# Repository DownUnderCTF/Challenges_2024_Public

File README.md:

<div align="center">

![banner][banner]

Files + Solutions for DownUnderCTF 2024 Challenges

[Website][website] | [CTFTime][ctftime] | [Discord][discord] | [Twitter][twitter]

[banner]: https://files.catbox.moe/vlniki.png
[website]: https://downunderctf.com
[ctftime]: https://ctftime.org/event/2284
[discord]: https://duc.tf/discord
[twitter]: https://twitter.com/downunderctf

</div>

---

# beginner
|                             Challenge                              |   Author   | Category | Solves |
| ------------------------------------------------------------------ | ---------- | -------- | -----: |
| [tldr please summarise](./beginner/tldr-please-summarise)          | Nosurf     | misc     |   1081 |
| [parrot the emu](./beginner/parrot-the-emu)                        | richighimi | web      |    993 |
| [Sun Zi's Perfect Math Class](./beginner/sunzi-perfect-math-class) | wednesday  | crypto   |    801 |
| [zoo feedback form](./beginner/zoo-feedback-form)                  | richighimi | web      |    693 |
| [shufflebox](./beginner/shufflebox)                                | hashkitten | crypto   |    582 |
| [number mashing](./beginner/number-mashing)                        | joseph     | rev      |    299 |
| [Intercepted Transmissions](./beginner/intercepted-transmissions)  | Pix        | misc     |    275 |
| [vector overflow](./beginner/vector-overflow)                      | joseph     | pwn      |    239 |
| [yawa](./beginner/yawa)                                            | joseph     | pwn      |    184 |
| [sssshhhh](./beginner/sssshhhh)                                    | Pix        | rev      |     81 |

# crypto
|                          Challenge                          |   Author   | Difficulty | Solves |
| ----------------------------------------------------------- | ---------- | ---------- | -----: |
| [decrypt then eval](./crypto/decrypt-then-eval)             | joseph     | easy       |    197 |
| [my array generator](./crypto/my-array-generator)           | wednesday  | easy       |     60 |
| [V for Vieta](./crypto/v-for-vieta)                         | wednesday  | easy       |     55 |
| [three line crypto](./crypto/three-line-crypto)             | hashkitten | medium     |     44 |
| [super party computation](./crypto/super-party-computation) | wednesday  | medium     |     13 |
| [Poly1305 OTM](./crypto/poly1305-otm)                       | joseph     | medium     |      6 |
| [AES](./crypto/aes)                                         | wednesday  | hard       |      2 |
| [kyber decryption oracle](./crypto/kyber-decryption-oracle) | joseph     | hard       |      1 |

# pwn
|                       Challenge                        |     Author      | Difficulty | Solves |
| ------------------------------------------------------ | --------------- | ---------- | -----: |
| [sign in](./pwn/sign-in)                               | joseph          | easy       |     95 |
| [pac shell](./pwn/pac-shell)                           | joseph          | easy       |     55 |
| [sheep farm simulator](./pwn/sheep-farm-simulator)     | joseph          | medium     |     21 |
| [Faulty Kernel](./pwn/faulty-kernel)                   | toasterpwn      | hard       |     15 |
| [ESPecially secure boot](./pwn/especially-secure-boot) | joseph, HexF    | medium     |      3 |
| [mirage](./pwn/mirage)                                 | grub and anvbis | hard       |      1 |

# rev
|                            Challenge                             |        Author         | Difficulty | Solves |
| ---------------------------------------------------------------- | --------------------- | ---------- | -----: |
| [rusty vault](./rev/rusty-vault)                                 | 1nval1d (Cybears)     | easy       |     81 |
| [jmp flag](./rev/jmp-flag)                                       | joseph                | easy       |     71 |
| [pressing buttons](./rev/pressing-buttons)                       | joseph                | medium     |     34 |
| [dungeon](./rev/dungeon)                                         | joseph                | medium     |     22 |
| [Ternary Brained](./rev/ternary-brained)                         | @jscarsbrook and @pix | medium     |     15 |
| [average assembly assignment](./rev/average-assembly-assignment) | joseph                | medium     |     13 |
| [adorable encrypted animal](./rev/adorable-encrypted-animal)     | joseph                | hard       |      3 |

# web
|                   Challenge                    |    Author    | Difficulty | Solves |
| ---------------------------------------------- | ------------ | ---------- | -----: |
| [co2](./web/co2)                               | n00b.master. | easy       |    289 |
| [hah got em](./web/hah-got-em)                 | ghostccamm   | easy       |    173 |
| [i am confusion](./web/i-am-confusion)         | richighimi   | medium     |    113 |
| [co2v2](./web/co2v2)                           | n00b.master. | medium     |     59 |
| [sniffy](./web/sniffy)                         | hashkitten   | easy       |     58 |
| [waifu](./web/waifu)                           | ghostccamm   | medium     |     20 |
| [Prisoner Processor](./web/prisoner-processor) | ghostccamm   | hard       |     17 |

# hardware
|                 Challenge                 |   Author    | Difficulty | Solves |
| ----------------------------------------- | ----------- | ---------- | -----: |
| [Sounds Nice](./hardware/sounds-nice)     | HexF        | easy       |    125 |
| [I See](./hardware/i-see)                 | HexF        | easy       |     61 |
| [The Door](./hardware/the-door)           | HexF        | medium     |     15 |
| [Crash Landing](./hardware/crash-landing) | HexF        | medium     |     12 |
| [sirkit](./hardware/sirkit)               | HexF        | hard       |      4 |
| [Birdloader](./hardware/birdloader)       | HexF, Jamie | medium     |      2 |
| [DUCTF](./hardware/ductf)                 | HexF        | hard       |      0 |

# forensics
|                          Challenge                          |       Author       | Difficulty | Solves |
| ----------------------------------------------------------- | ------------------ | ---------- | -----: |
| [Baby's First Forensics](./forensics/babys-first-forensics) | Pix                | beginner   |    920 |
| [SAM I AM](./forensics/samiam)                              | TurboPenguin       | beginner   |    545 |
| [Bad Policies](./forensics/badpolicies)                     | TurboPenguin       | beginner   |    386 |
| [Macro Magic](./forensics/macromagic)                       | TurboPenguin & Pix | easy       |    146 |
| [emuc2](./forensics/emuc2)                                  | BootlegSorcery@    | easy       |    117 |
| [Lost in Memory](./forensics/lostinmemory)                  | TurboPenguin       | medium     |     42 |

# osint
|                       Challenge                        |   Author   | Difficulty | Solves |
| ------------------------------------------------------ | ---------- | ---------- | -----: |
| [offtheramp](./osint/offtheramp)                       | Anon       | beginner   |    851 |
| [cityviews](./osint/cityviews)                         | Anon       | easy       |    631 |
| [Bridget Lives](./osint/bridget-lives)                 | a_metre    | easy       |    505 |
| [back to the jungle](./osint/back-to-the-jungle)       | ghostccamm | easy       |    460 |
| [They're Making Decoys](./osint/they-re-making-decoys) | Nosurf     | medium     |    190 |
| [marketing](./osint/marketing)                         | ghostccamm | beginner   |    187 |

# misc
|                       Challenge                       |        Author         | Difficulty | Solves |
| ----------------------------------------------------- | --------------------- | ---------- | -----: |
| [discord](./misc/discord)                             | DUCTF                 | beginner   |    855 |
| [survey](./misc/survey)                               | DUCTF                 | beginner   |    446 |
| [Wacky Recipe](./misc/wackyrecipe)                    | TurboPenguin & joseph | easy       |    152 |
| [DNAdecay](./misc/dnadecay)                           | BootlegSorcery@       | easy       |    148 |
| [WebSocket VPN](./misc/wsvpn)                         | jscarsbrook           | medium     |     23 |
| [the other minimal php](./misc/the-other-minimal-php) | hashkitten            | medium     |     22 |
| [mkductfiso](./misc/mkductfiso)                       | Pix && joseph         | medium     |     19 |
| [pkijs<](./misc/pkijs-lt)                             | joseph                | medium     |      7 |
| [pkijs=](./misc/pkijs-eq)                             | joseph                | medium     |      1 |

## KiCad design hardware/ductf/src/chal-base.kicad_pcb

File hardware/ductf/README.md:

# DUCTF

This challenge involves an attack on the DESFire protocol, when the random nonce generated by the reader is known.
The random nonce in this case is generated using the hardware randomness of the RP2040.
In the RP2040, if the CPU clock is a harmonic of the internal ring oscillator, the random number generator is entirely predictable (yielding either all 1s or all 0s).

We can then use the reader as an encryption primitive through its use of CBC encryption to forge a DESFire session key with the reader.
We can thus communicate with the reader, which will write the flag to our card.

**Category**: Hardware / Crypto

**Difficulty**: Hard

**Author**: HexF

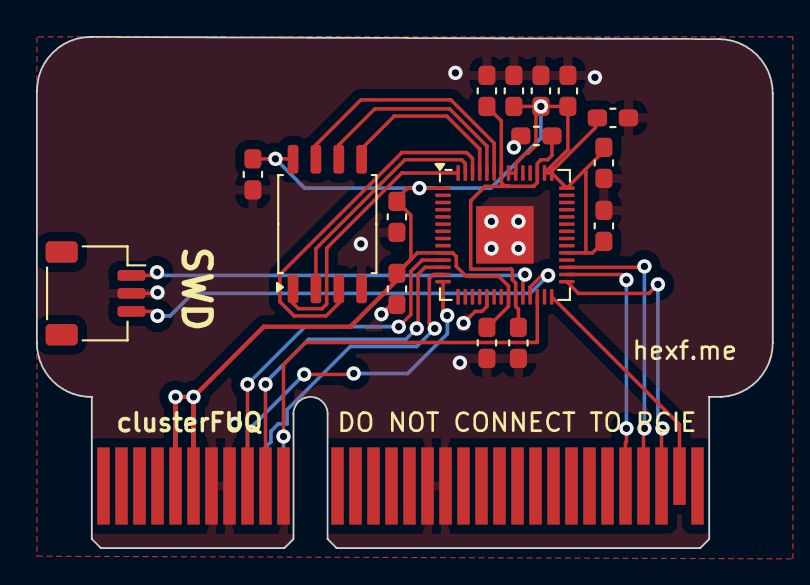
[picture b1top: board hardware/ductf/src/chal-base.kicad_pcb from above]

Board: 2 copper layers, 40.9 x 28.4 mm, 17 parts (0 on the bottom side), 20 nets.

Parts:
C101, C103, C104, C105, C106, C107, C108, C109, C110, C111, C112: 100nF; C_0603_1608Metric_Pad1.08x0.95mm_HandSolder
C102, C113: 1uF; C_0603_1608Metric_Pad1.08x0.95mm_HandSolder
J1: clusterFUQ_Connector; BUS_PCIexpress_x4
J101: Conn_01x03_Pin; JST_SH_SM03B-SRSS-TB_1x03-1MP_P1.00mm_Horizontal
U101: RP2040; QFN-56-1EP_7x7mm_P0.4mm_EP3.2x3.2mm
U102: W25Q16JVSS; SOIC-8_5.23x5.23mm_P1.27mm

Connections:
+3V3: C101.1, C102.1, C103.1, C104.1, C105.1, C106.1, C107.1, C108.1, C109.1, C110.1, J1.A5 (+3V3), J1.A6 (+3V3), J1.B5 (+3V3), J1.B6 (+3V3), U101.1 (IOVDD), U101.10 (IOVDD), U101.22 (IOVDD), U101.33 (IOVDD), U101.42 (IOVDD), U101.43 (ADC_AVDD), U101.44 (VREG_IN), U101.48 (USB_VDD), U101.49 (IOVDD), U102.8 (VCC)
/CH_CS: J1.B10 (CS), U101.12 (GPIO9)
/CH_MISO: J1.A9 (MISO), U101.14 (GPIO11)
/CH_MOSI: J1.B9 (MOSI), U101.11 (GPIO8)
/CH_SCK: J1.A10 (SCK), U101.13 (GPIO10)
/MISO: J1.B29 (IO19), U101.31 (GPIO20)
/MOSI: J1.B28 (IO20), U101.30 (GPIO19)
/QSPI.CK: U101.52 (QSPI_SCLK), U102.6 (CLK)
/QSPI.D0: U101.53 (QSPI_SD0), U102.5 (DI(IO0))
/QSPI.D1: U101.55 (QSPI_SD1), U102.2 (DO(IO1))
/QSPI.D2: U101.54 (QSPI_SD2), U102.3 (~WP(IO2))
/QSPI.D3: U101.51 (QSPI_SD3), U102.7 (~RESET(IO3))
/QSPI.SS: U101.56 (QSPI_SS), U102.1 (~CS)
/RC522_CS: J1.B31 (IO17), U101.28 (GPIO17)
/SCK: J1.B30 (IO18), U101.29 (GPIO18)
/~RESET: J1.A11 (~RESET), U101.26 (RUN)
GND: C101.2, C102.2, C103.2, C104.2, C105.2, C106.2, C107.2, C108.2, C109.2, C110.2, C111.1, C112.1, C113.1, J1.A7 (GND), J1.A8 (GND), J1.B7 (GND), J1.B8 (GND), J1.B11 (GND), J1.B17 (GND), J1.B18 (GND), J101.2, U101.19 (TESTEN), U101.57 (GND), U102.4 (GND)
unnamed: J101.1, U101.24 (SWCLK)
unnamed: J101.3, U101.25 (SWD)
unnamed: C111.2, C112.2, C113.2, U101.23 (DVDD), U101.45 (VREG_VOUT), U101.50 (DVDD)

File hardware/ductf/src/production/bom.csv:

Designator,Footprint,Quantity,Value,LCSC Part #
"C101, C103, C104, C105, C106, C107, C108, C109, C110, C111, C112",0603,11,100nF,C14663
"C102, C113",0603,2,1uF,C15849
J101,JST_SH_SM03B-SRSS-TB_1x03-1MP_P1.00mm_Horizontal,1,Conn_01x03_Pin,C160403
U101,QFN-56-1EP_7x7mm_P0.4mm_EP3.2x3.2mm,1,RP2040,
U102,SOIC-8_5.23x5.23mm_P1.27mm,1,W25Q16JVSS,C131025

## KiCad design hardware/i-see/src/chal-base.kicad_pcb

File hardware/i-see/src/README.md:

# Assembly

1. Flash EEPROM with `eeprom.bin` (256 bytes).
2. Solder 'Write Protect' Jumper

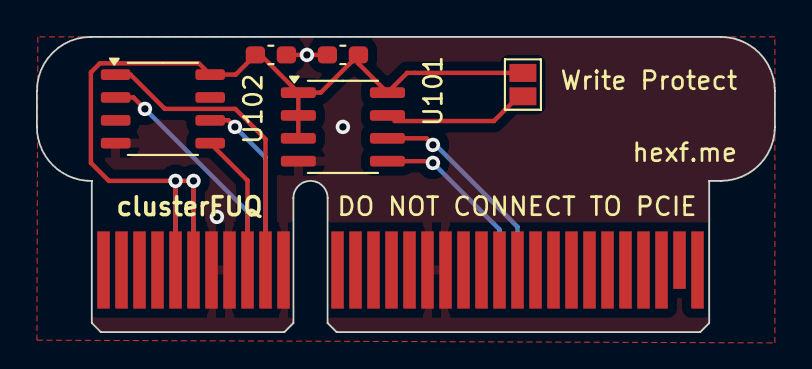
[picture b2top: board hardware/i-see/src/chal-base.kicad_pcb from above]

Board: 2 copper layers, 41.0 x 16.4 mm, 6 parts (0 on the bottom side), 9 nets.

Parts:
C101, C102: 100nF; C_0603_1608Metric_Pad1.08x0.95mm_HandSolder
J1: clusterFUQ_Connector; BUS_PCIexpress_x4
JP101: Jumper_2_Bridged; SolderJumper-2_P1.3mm_Open_Pad1.0x1.5mm
U101: M24C02-WMN; SOIC-8_3.9x4.9mm_P1.27mm
U102: NB25Q40A; SOP-8_3.9x4.9mm_P1.27mm

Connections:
+3V3: C101.1, C102.1, J1.A5 (+3V3), J1.A6 (+3V3), J1.B5 (+3V3), J1.B6 (+3V3), JP101.1 (A), U101.1 (E0), U101.2 (E1), U101.3 (E2), U101.8 (VCC), U102.8 (VCC)
/CH_CS: J1.B10 (CS), U102.1 (~CS)
/CH_MISO: J1.A9 (MISO), U102.2 (DO(IO1))
/CH_MOSI: J1.B9 (MOSI), U102.5 (DI(IO0))
/CH_SCK: J1.A10 (SCK), U102.6 (CLK)
/SCL: J1.A22 (IO5), U101.6 (SCL)
/SDA: J1.A21 (IO4), U101.5 (SDA)
GND: C101.2, C102.2, J1.A7 (GND), J1.A8 (GND), J1.B7 (GND), J1.B8 (GND), J1.B11 (GND), J1.B17 (GND), J1.B18 (GND), U101.4 (VSS), U102.4 (GND)
unnamed: JP101.2 (B), U101.7 (~WC)

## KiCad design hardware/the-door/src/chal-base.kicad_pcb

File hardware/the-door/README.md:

The Door
======================

- **Category**: hardware
- **Difficulty**: medium
- **Author**: HexF
- **Tags**: 

I lost the remote to the plane hanger door. Help kiwi get back in the air!

NOTE: Your code has a 5 minute runtime limit

---

### Handout files

- [./publish/schematic.pdf](./publish/schematic.pdf)

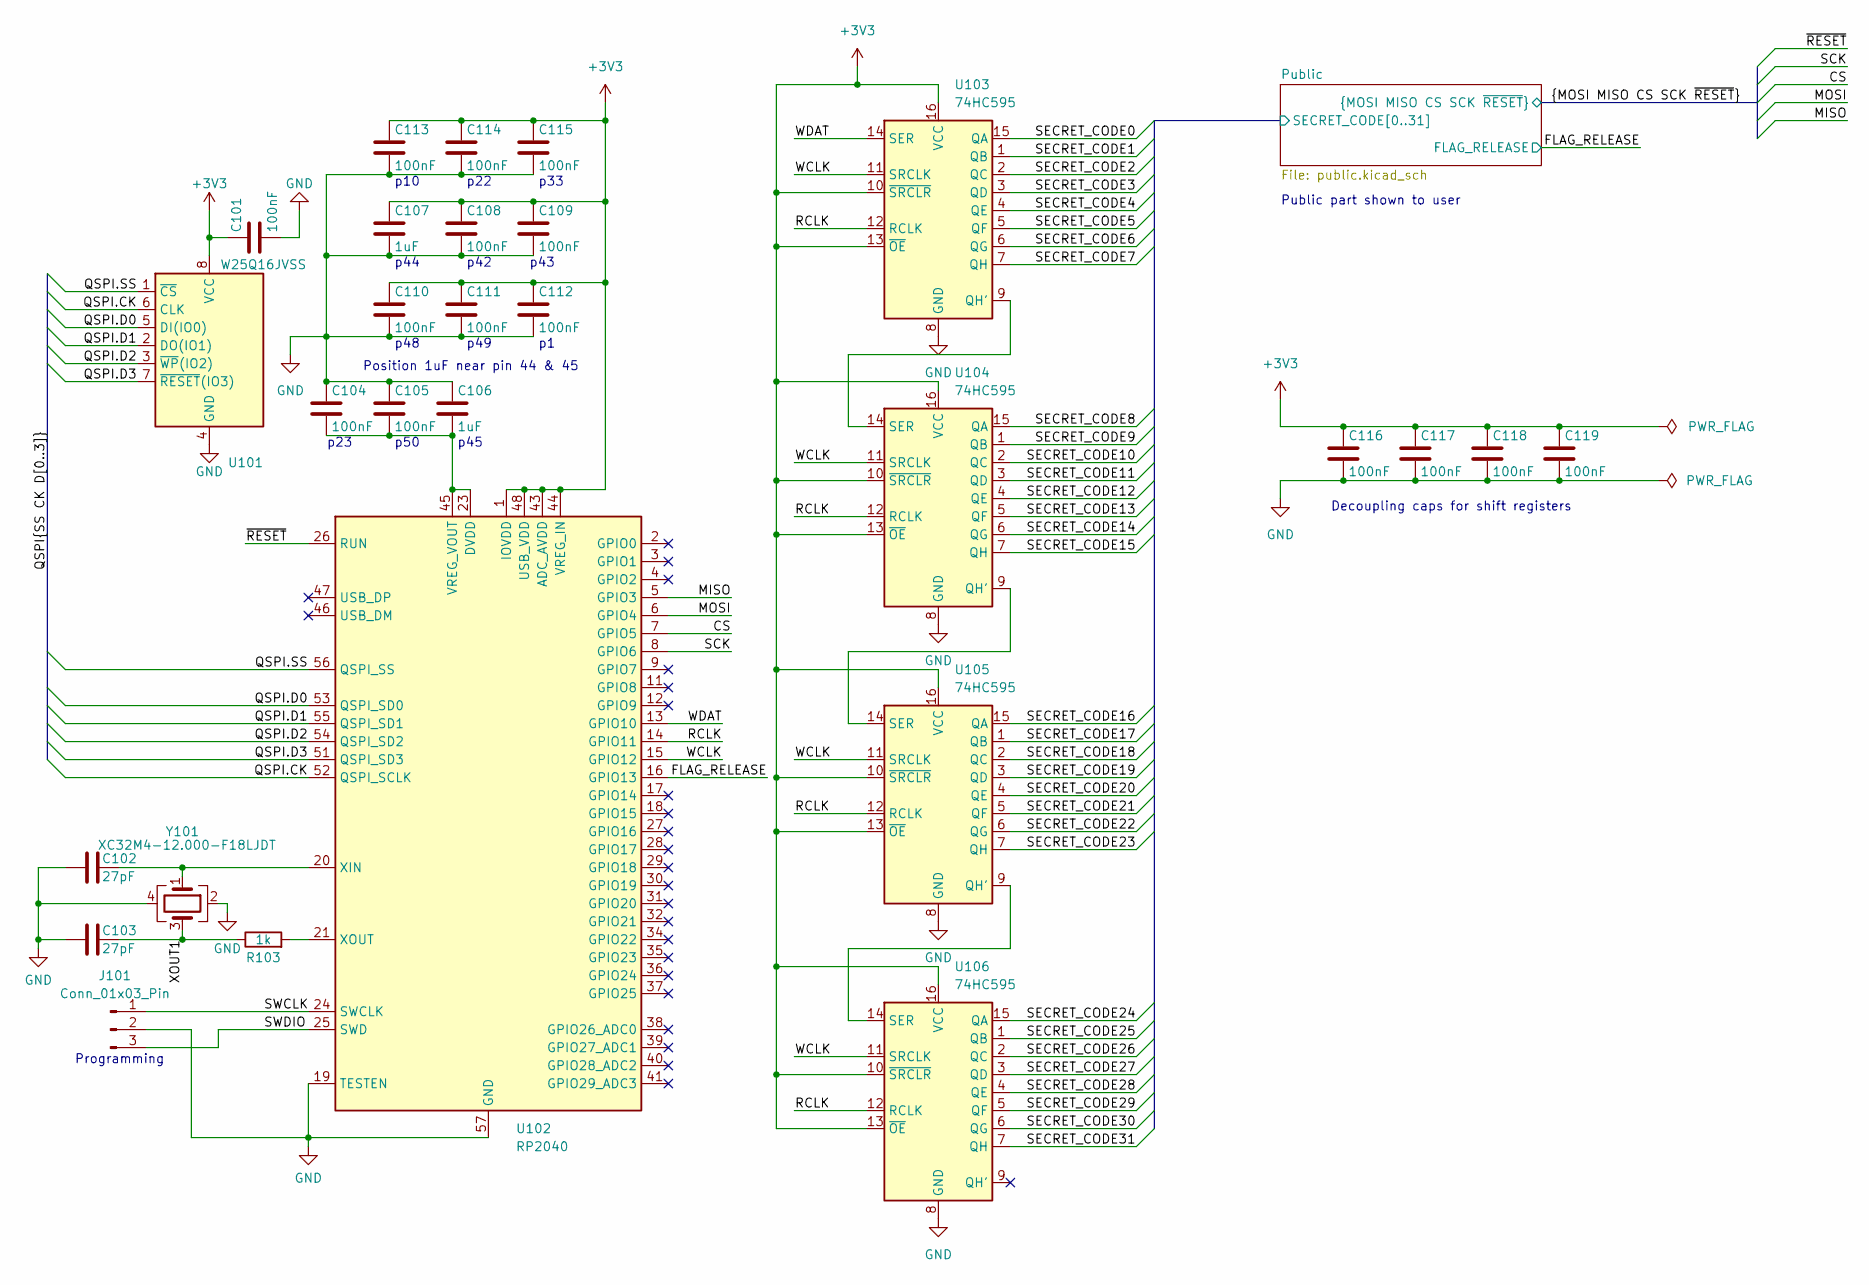
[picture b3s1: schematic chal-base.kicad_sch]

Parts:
C101, C104, C105, C108, C109, C110, C111, C112, C113, C114, C115, C116, C117, C118, C119: 100nF; C_0603_1608Metric_Pad1.08x0.95mm_HandSolder; LCSC C14663
C102, C103: 27pF; C_0603_1608Metric_Pad1.08x0.95mm_HandSolder; LCSC C107045
C106, C107: 1uF; C_0603_1608Metric_Pad1.08x0.95mm_HandSolder; LCSC C15849
J101: Conn_01x03_Pin; JST_SH_SM03B-SRSS-TB_1x03-1MP_P1.00mm_Horizontal; LCSC C160403
R103: 1k; R_0603_1608Metric_Pad0.98x0.95mm_HandSolder; LCSC C21190
U101: W25Q16JVSS; SOIC-8_5.23x5.23mm_P1.27mm; LCSC C131025
U102: RP2040; QFN-56-1EP_7x7mm_P0.4mm_EP3.2x3.2mm; LCSC C2040
U103, U104, U105, U106: 74HC595; SOP-16_3.9x9.9mm_P1.27mm; LCSC C2929943
Y101: XC32M4-12.000-F18LJDT; Crystal_SMD_3225-4Pin_3.2x2.5mm_HandSoldering; LCSC C2890217

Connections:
+3V3: C101.1, C107.1, C108.1, C109.1, C110.1, C111.1, C112.1, C113.1, C114.1, C115.1, C116.1, C117.1, C118.1, C119.1, U101.8 (VCC), U102.1 (IOVDD), U102.10 (IOVDD), U102.22 (IOVDD), U102.33 (IOVDD), U102.42 (IOVDD), U102.43 (ADC_AVDD), U102.44 (VREG_IN), U102.48 (USB_VDD), U102.49 (IOVDD), U103.10 (~SRCLR), U103.13 (~OE), U103.16 (VCC), U104.10 (~SRCLR), U104.13 (~OE), U104.16 (VCC), U105.10 (~SRCLR), U105.13 (~OE), U105.16 (VCC), U106.10 (~SRCLR), U106.13 (~OE), U106.16 (VCC); also elsewhere on the board
/CS: U102.7 (GPIO5); also elsewhere on the board
/FLAG_RELEASE: U102.16 (GPIO13); also elsewhere on the board
/MISO: U102.5 (GPIO3); also elsewhere on the board
/MOSI: U102.6 (GPIO4); also elsewhere on the board
/Public/SECRET_CODE0: U103.15 (QA); also elsewhere on the board
/Public/SECRET_CODE1: U103.1 (QB); also elsewhere on the board
/Public/SECRET_CODE2: U103.2 (QC); also elsewhere on the board
/Public/SECRET_CODE3: U103.3 (QD); also elsewhere on the board
/Public/SECRET_CODE4: U103.4 (QE); also elsewhere on the board
/Public/SECRET_CODE5: U103.5 (QF); also elsewhere on the board
/Public/SECRET_CODE6: U103.6 (QG); also elsewhere on the board
/Public/SECRET_CODE7: U103.7 (QH); also elsewhere on the board
/Public/SECRET_CODE8: U104.15 (QA); also elsewhere on the board
/Public/SECRET_CODE9: U104.1 (QB); also elsewhere on the board
/Public/SECRET_CODE10: U104.2 (QC); also elsewhere on the board
/Public/SECRET_CODE11: U104.3 (QD); also elsewhere on the board
/Public/SECRET_CODE12: U104.4 (QE); also elsewhere on the board
/Public/SECRET_CODE13: U104.5 (QF); also elsewhere on the board
/Public/SECRET_CODE14: U104.6 (QG); also elsewhere on the board
/Public/SECRET_CODE15: U104.7 (QH); also elsewhere on the board
/Public/SECRET_CODE16: U105.15 (QA); also elsewhere on the board
/Public/SECRET_CODE17: U105.1 (QB); also elsewhere on the board
/Public/SECRET_CODE18: U105.2 (QC); also elsewhere on the board
/Public/SECRET_CODE19: U105.3 (QD); also elsewhere on the board
/Public/SECRET_CODE20: U105.4 (QE); also elsewhere on the board
/Public/SECRET_CODE21: U105.5 (QF); also elsewhere on the board
/Public/SECRET_CODE22: U105.6 (QG); also elsewhere on the board
/Public/SECRET_CODE23: U105.7 (QH); also elsewhere on the board
/Public/SECRET_CODE24: U106.15 (QA); also elsewhere on the board
/Public/SECRET_CODE25: U106.1 (QB); also elsewhere on the board
/Public/SECRET_CODE26: U106.2 (QC); also elsewhere on the board
/Public/SECRET_CODE27: U106.3 (QD); also elsewhere on the board
/Public/SECRET_CODE28: U106.4 (QE); also elsewhere on the board
/Public/SECRET_CODE29: U106.5 (QF); also elsewhere on the board
/Public/SECRET_CODE30: U106.6 (QG); also elsewhere on the board
/Public/SECRET_CODE31: U106.7 (QH); also elsewhere on the board
/QSPI.CK: U101.6 (CLK), U102.52 (QSPI_SCLK)
/QSPI.D0: U101.5 (DI(IO0)), U102.53 (QSPI_SD0)
/QSPI.D1: U101.2 (DO(IO1)), U102.55 (QSPI_SD1)
/QSPI.D2: U101.3 (~WP(IO2)), U102.54 (QSPI_SD2)
/QSPI.D3: U101.7 (~RESET(IO3)), U102.51 (QSPI_SD3)
/QSPI.SS: U101.1 (~CS), U102.56 (QSPI_SS)
/RCLK: U102.14 (GPIO11), U103.12 (RCLK), U104.12 (RCLK), U105.12 (RCLK), U106.12 (RCLK)
/SCK: U102.8 (GPIO6); also elsewhere on the board
/SWCLK: J101.1, U102.24 (SWCLK)
/SWDIO: J101.3, U102.25 (SWD)
/WCLK: U102.15 (GPIO12), U103.11 (SRCLK), U104.11 (SRCLK), U105.11 (SRCLK), U106.11 (SRCLK)
/WDAT: U102.13 (GPIO10), U103.14 (SER)
/XOUT1: C103.2, R103.1, Y101.3
/~RESET: U102.26 (RUN); also elsewhere on the board
GND: C101.2, C102.1, C103.1, C104.1, C105.1, C106.1, C107.2, C108.2, C109.2, C110.2, C111.2, C112.2, C113.2, C114.2, C115.2, C116.2, C117.2, C118.2, C119.2, J101.2, U101.4 (GND), U102.19 (TESTEN), U102.57 (GND), U103.8 (GND), U104.8 (GND), U105.8 (GND), U106.8 (GND), Y101.2, Y101.4; also elsewhere on the board
unnamed: C104.2, C105.2, C106.2, U102.23 (DVDD), U102.45 (VREG_VOUT), U102.50 (DVDD)
unnamed: C102.2, U102.20 (XIN), Y101.1
unnamed: R103.2, U102.21 (XOUT)
unnamed: U103.9 (QH'), U104.14 (SER)
unnamed: U104.9 (QH'), U105.14 (SER)
unnamed: U105.9 (QH'), U106.14 (SER)

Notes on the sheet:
p50
p44
Public part shown to user
p33
p22
Programming
p45
p23
p48
Decoupling caps for shift registers
p49
Position 1uF near pin 44 & 45
p10
p43
p42

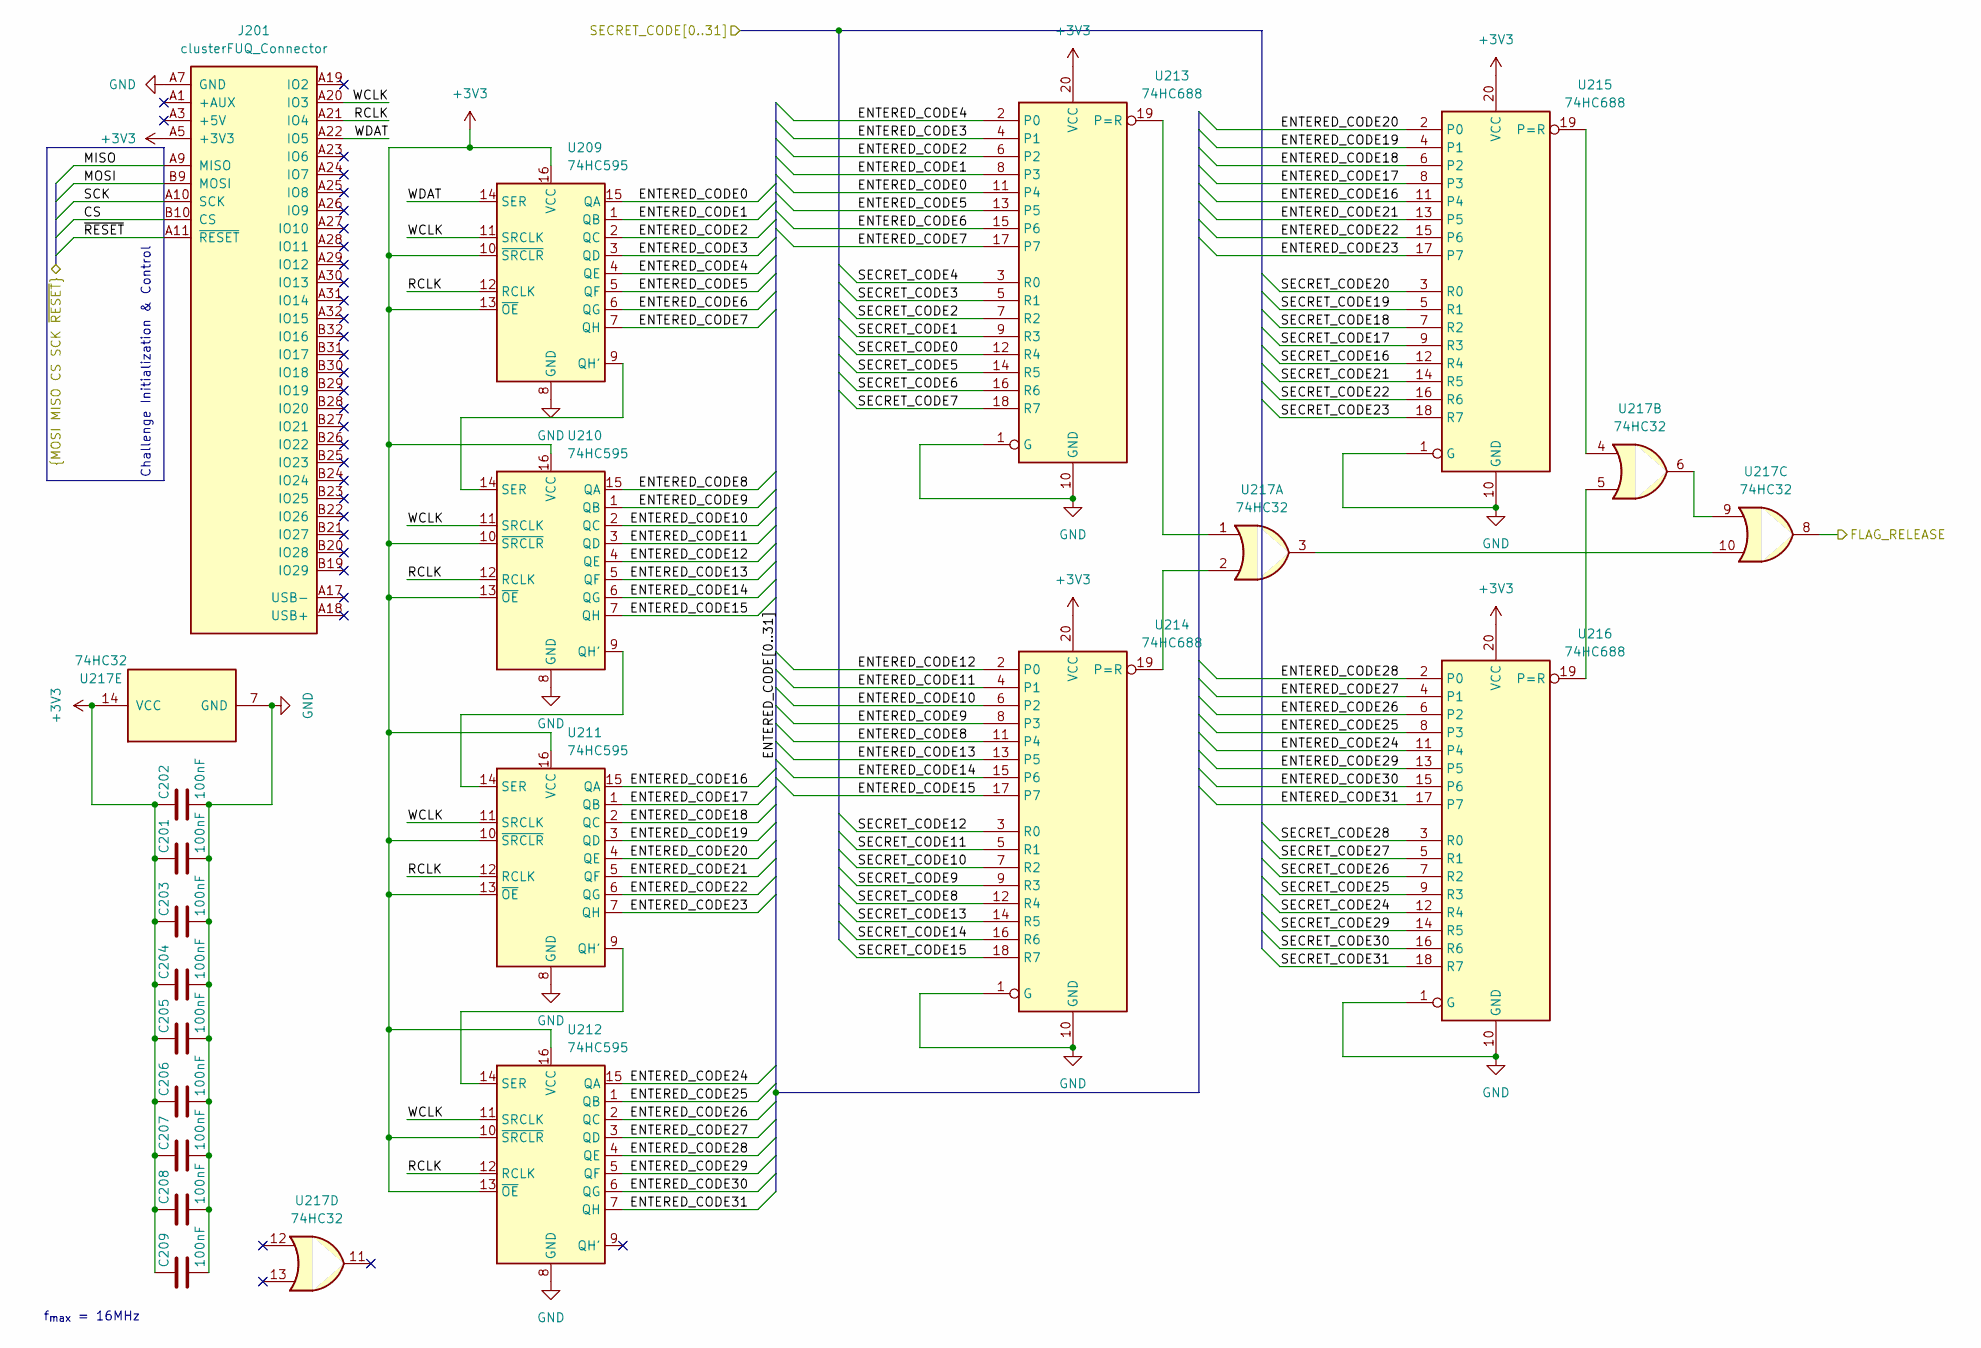
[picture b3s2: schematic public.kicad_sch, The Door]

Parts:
C201, C202, C203, C204, C205, C206, C207, C208, C209: 100nF; C_0603_1608Metric_Pad1.08x0.95mm_HandSolder; LCSC C14663
J201: clusterFUQ_Connector; BUS_PCIexpress_x4
U209, U210, U211, U212: 74HC595; SOP-16_3.9x9.9mm_P1.27mm; LCSC C2929943
U213, U214, U215, U216: 74HC688; SOIC-20W_7.5x12.8mm_P1.27mm; LCSC C88042
U217: 74HC32; SOIC-14_3.9x8.7mm_P1.27mm; LCSC C5632

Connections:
+3V3: C201.1, C202.1, C203.1, C204.1, C205.1, C206.1, C207.1, C208.1, C209.1, J201.A5 (+3V3), J201.A6 (+3V3), J201.B5 (+3V3), J201.B6 (+3V3), U209.10 (~SRCLR), U209.13 (~OE), U209.16 (VCC), U210.10 (~SRCLR), U210.13 (~OE), U210.16 (VCC), U211.10 (~SRCLR), U211.13 (~OE), U211.16 (VCC), U212.10 (~SRCLR), U212.13 (~OE), U212.16 (VCC), U213.20 (VCC), U214.20 (VCC), U215.20 (VCC), U216.20 (VCC), U217.14 (VCC); also elsewhere on the board
/CS: J201.B10 (CS); also elsewhere on the board
/FLAG_RELEASE: U217.8; also elsewhere on the board
/MISO: J201.A9 (MISO); also elsewhere on the board
/MOSI: J201.B9 (MOSI); also elsewhere on the board
/Public/ENTERED_CODE0: U209.15 (QA), U213.11 (P4)
/Public/ENTERED_CODE1: U209.1 (QB), U213.8 (P3)
/Public/ENTERED_CODE2: U209.2 (QC), U213.6 (P2)
/Public/ENTERED_CODE3: U209.3 (QD), U213.4 (P1)
/Public/ENTERED_CODE4: U209.4 (QE), U213.2 (P0)
/Public/ENTERED_CODE5: U209.5 (QF), U213.13 (P5)
/Public/ENTERED_CODE6: U209.6 (QG), U213.15 (P6)
/Public/ENTERED_CODE7: U209.7 (QH), U213.17 (P7)
/Public/ENTERED_CODE8: U210.15 (QA), U214.11 (P4)
/Public/ENTERED_CODE9: U210.1 (QB), U214.8 (P3)
/Public/ENTERED_CODE10: U210.2 (QC), U214.6 (P2)
/Public/ENTERED_CODE11: U210.3 (QD), U214.4 (P1)
/Public/ENTERED_CODE12: U210.4 (QE), U214.2 (P0)
/Public/ENTERED_CODE13: U210.5 (QF), U214.13 (P5)
/Public/ENTERED_CODE14: U210.6 (QG), U214.15 (P6)
/Public/ENTERED_CODE15: U210.7 (QH), U214.17 (P7)
/Public/ENTERED_CODE16: U211.15 (QA), U215.11 (P4)
/Public/ENTERED_CODE17: U211.1 (QB), U215.8 (P3)
/Public/ENTERED_CODE18: U211.2 (QC), U215.6 (P2)
/Public/ENTERED_CODE19: U211.3 (QD), U215.4 (P1)
/Public/ENTERED_CODE20: U211.4 (QE), U215.2 (P0)
/Public/ENTERED_CODE21: U211.5 (QF), U215.13 (P5)
/Public/ENTERED_CODE22: U211.6 (QG), U215.15 (P6)
/Public/ENTERED_CODE23: U211.7 (QH), U215.17 (P7)
/Public/ENTERED_CODE24: U212.15 (QA), U216.11 (P4)
/Public/ENTERED_CODE25: U212.1 (QB), U216.8 (P3)
/Public/ENTERED_CODE26: U212.2 (QC), U216.6 (P2)
/Public/ENTERED_CODE27: U212.3 (QD), U216.4 (P1)
/Public/ENTERED_CODE28: U212.4 (QE), U216.2 (P0)
/Public/ENTERED_CODE29: U212.5 (QF), U216.13 (P5)
/Public/ENTERED_CODE30: U212.6 (QG), U216.15 (P6)
/Public/ENTERED_CODE31: U212.7 (QH), U216.17 (P7)
/Public/RCLK: J201.A21 (IO4), U209.12 (RCLK), U210.12 (RCLK), U211.12 (RCLK), U212.12 (RCLK)
/Public/SECRET_CODE0: U213.12 (R4); also elsewhere on the board
/Public/SECRET_CODE1: U213.9 (R3); also elsewhere on the board
/Public/SECRET_CODE2: U213.7 (R2); also elsewhere on the board
/Public/SECRET_CODE3: U213.5 (R1); also elsewhere on the board
/Public/SECRET_CODE4: U213.3 (R0); also elsewhere on the board
/Public/SECRET_CODE5: U213.14 (R5); also elsewhere on the board
/Public/SECRET_CODE6: U213.16 (R6); also elsewhere on the board
/Public/SECRET_CODE7: U213.18 (R7); also elsewhere on the board
/Public/SECRET_CODE8: U214.12 (R4); also elsewhere on the board
/Public/SECRET_CODE9: U214.9 (R3); also elsewhere on the board
/Public/SECRET_CODE10: U214.7 (R2); also elsewhere on the board
/Public/SECRET_CODE11: U214.5 (R1); also elsewhere on the board
/Public/SECRET_CODE12: U214.3 (R0); also elsewhere on the board
/Public/SECRET_CODE13: U214.14 (R5); also elsewhere on the board
/Public/SECRET_CODE14: U214.16 (R6); also elsewhere on the board
/Public/SECRET_CODE15: U214.18 (R7); also elsewhere on the board
/Public/SECRET_CODE16: U215.12 (R4); also elsewhere on the board
/Public/SECRET_CODE17: U215.9 (R3); also elsewhere on the board
/Public/SECRET_CODE18: U215.7 (R2); also elsewhere on the board
/Public/SECRET_CODE19: U215.5 (R1); also elsewhere on the board
/Public/SECRET_CODE20: U215.3 (R0); also elsewhere on the board
/Public/SECRET_CODE21: U215.14 (R5); also elsewhere on the board
/Public/SECRET_CODE22: U215.16 (R6); also elsewhere on the board
/Public/SECRET_CODE23: U215.18 (R7); also elsewhere on the board
/Public/SECRET_CODE24: U216.12 (R4); also elsewhere on the board
/Public/SECRET_CODE25: U216.9 (R3); also elsewhere on the board
/Public/SECRET_CODE26: U216.7 (R2); also elsewhere on the board
/Public/SECRET_CODE27: U216.5 (R1); also elsewhere on the board
/Public/SECRET_CODE28: U216.3 (R0); also elsewhere on the board
/Public/SECRET_CODE29: U216.14 (R5); also elsewhere on the board
/Public/SECRET_CODE30: U216.16 (R6); also elsewhere on the board
/Public/SECRET_CODE31: U216.18 (R7); also elsewhere on the board
/Public/WCLK: J201.A20 (IO3), U209.11 (SRCLK), U210.11 (SRCLK), U211.11 (SRCLK), U212.11 (SRCLK)
/Public/WDAT: J201.A22 (IO5), U209.14 (SER)
/SCK: J201.A10 (SCK); also elsewhere on the board
/~RESET: J201.A11 (~RESET); also elsewhere on the board
GND: C201.2, C202.2, C203.2, C204.2, C205.2, C206.2, C207.2, C208.2, C209.2, J201.A7 (GND), J201.A8 (GND), J201.B7 (GND), J201.B8 (GND), J201.B11 (GND), J201.B17 (GND), J201.B18 (GND), U209.8 (GND), U210.8 (GND), U211.8 (GND), U212.8 (GND), U213.1 (G), U213.10 (GND), U214.1 (G), U214.10 (GND), U215.1 (G), U215.10 (GND), U216.1 (G), U216.10 (GND), U217.7 (GND); also elsewhere on the board
unnamed: U209.9 (QH'), U210.14 (SER)
unnamed: U210.9 (QH'), U211.14 (SER)
unnamed: U211.9 (QH'), U212.14 (SER)
unnamed: U213.19 (P=R), U217.1
unnamed: U214.19 (P=R), U217.2
unnamed: U215.19 (P=R), U217.4
unnamed: U216.19 (P=R), U217.5
unnamed: U217.6, U217.9
unnamed: U217.3, U217.10

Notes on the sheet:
f_{max} = 16MHz
Challenge Initialization & Control

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
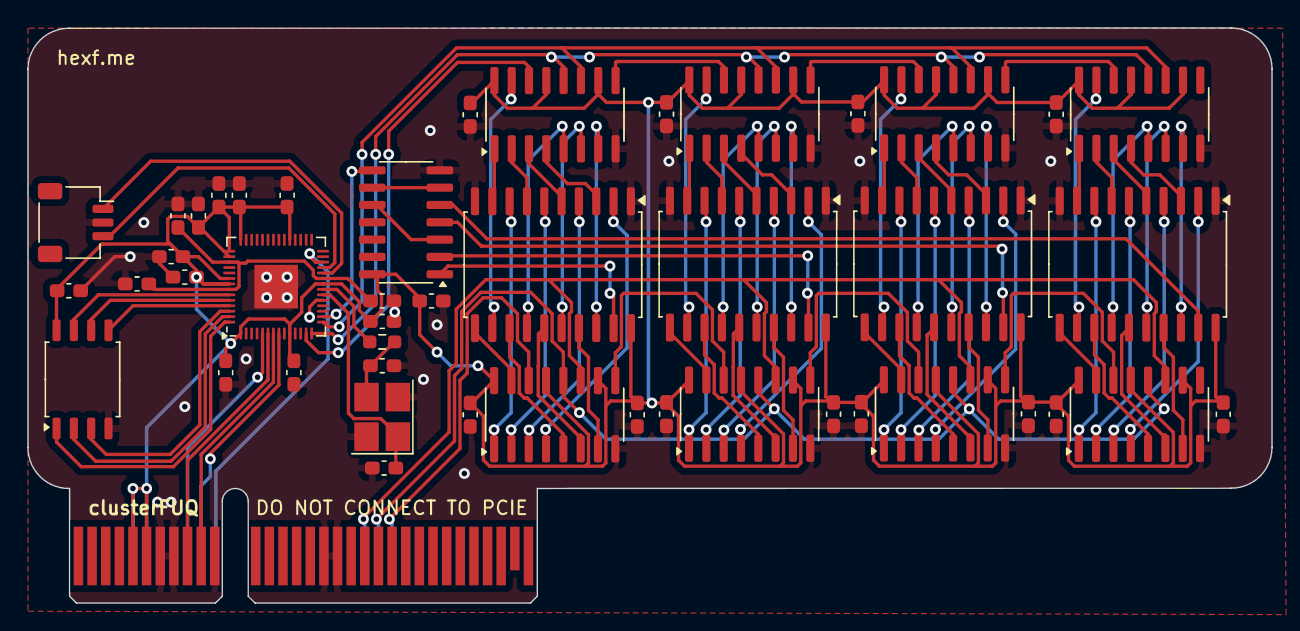
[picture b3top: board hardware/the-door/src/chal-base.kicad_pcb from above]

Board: 2 copper layers, 91.2 x 42.2 mm, 47 parts (0 on the bottom side), 102 nets.

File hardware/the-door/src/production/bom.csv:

Designator,Footprint,Quantity,Value,LCSC Part #
"C101, C104, C105, C108, C109, C110, C111, C112, C113, C114, C115, C116, C117, C118, C119, C201, C202, C203, C204, C205, C206, C207, C208, C209",0603,24,100nF,C14663
"C102, C103",0603,2,27pF,C107045
"C106, C107",0603,2,1uF,C15849
J101,JST_SH_SM03B-SRSS-TB_1x03-1MP_P1.00mm_Horizontal,1,Conn_01x03_Pin,C160403
R103,0603,1,1k,C21190
U101,SOIC-8_5.23x5.23mm_P1.27mm,1,W25Q16JVSS,C131025
U102,QFN-56-1EP_7x7mm_P0.4mm_EP3.2x3.2mm,1,RP2040,C2040
"U103, U104, U105, U106, U209, U210, U211, U212",SOP-16_3.9x9.9mm_P1.27mm,8,74HC595,C2929943
"U213, U214, U215, U216",SOIC-20W_7.5x12.8mm_P1.27mm,4,74HC688,C88042
U217,SOIC-14_3.9x8.7mm_P1.27mm,1,74HC32,C5632
Y101,Crystal_SMD_3225-4Pin_3.2x2.5mm_HandSoldering,1,XC32M4-12.000-F18LJDT,C2890217

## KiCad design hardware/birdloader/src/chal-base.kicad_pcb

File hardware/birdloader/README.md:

Birdloader
======================

- **Category**: hardware
- **Difficulty**: medium
- **Author**: HexF, Jamie
- **Tags**: 

The kiwis can't turn on their device anymore. Maybe you can get it to work?

We have connected your RP2040 to what appears to be a 9600baud serial port. You TX (device RXes) on pin 8; you RX (device TXes) on pin 9.

---

### Handout files

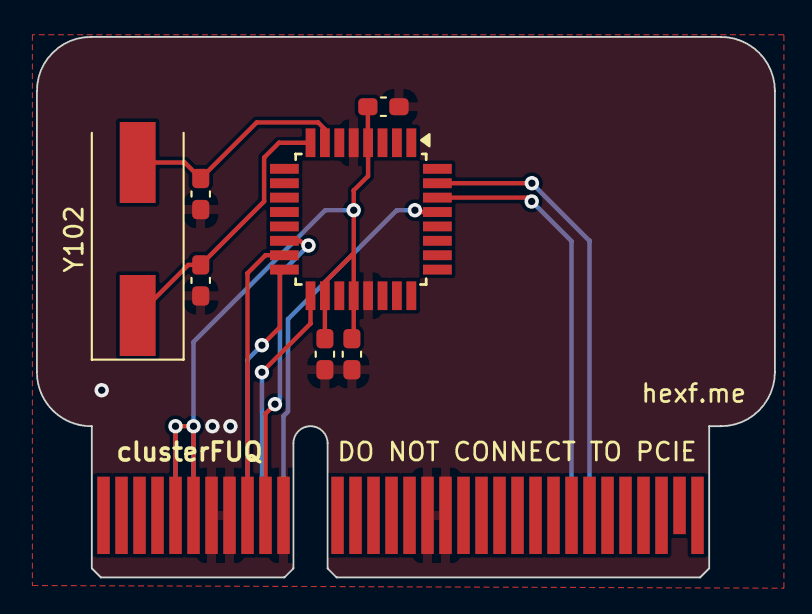
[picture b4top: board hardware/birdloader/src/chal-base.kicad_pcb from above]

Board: 2 copper layers, 41.0 x 30.0 mm, 8 parts (0 on the bottom side), 11 nets.

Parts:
C101, C102: 22pF; C_0603_1608Metric_Pad1.08x0.95mm_HandSolder
C103: 100nF; C_0603_1608Metric_Pad1.08x0.95mm_HandSolder
C104, C105: 1uF; C_0603_1608Metric_Pad1.08x0.95mm_HandSolder
J1: clusterFUQ_Connector; BUS_PCIexpress_x4
U101: ATmega328PB-A; TQFP-32_7x7mm_P0.8mm
Y102: X49SM8MSD2SC; Crystal_SMD_HC49-SD

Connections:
+3V3: C103.1, C104.1, C105.1, J1.A5 (+3V3), J1.A6 (+3V3), J1.B5 (+3V3), J1.B6 (+3V3), U101.4 (VCC), U101.18 (AVCC), U101.20 (AREF)
/CH_RX: J1.A25 (IO8), U101.30 (PD0)
/CH_TX: J1.A26 (IO9), U101.31 (PD1)
/SPI_CS: J1.B10 (CS), U101.14 (PB2)
/SPI_MISO: J1.A9 (MISO), U101.16 (PB4)
/SPI_MOSI: J1.B9 (MOSI), U101.15 (PB3)
/SPI_SCK: J1.A10 (SCK), U101.17 (PB5)
/XTAL1: C102.1, U101.7 (XTAL1/PB6), Y102.2
/XTAL2: C101.1, U101.8 (XTAL2/PB7), Y102.1
/~RESET: J1.A11 (~RESET), U101.29 (~RESET/PC6)
GND: C101.2, C102.2, C103.2, C104.2, C105.2, J1.A7 (GND), J1.A8 (GND), J1.B7 (GND), J1.B8 (GND), J1.B11 (GND), J1.B17 (GND), J1.B18 (GND), U101.5 (GND), U101.21 (GND)

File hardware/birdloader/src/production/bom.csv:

Designator,Footprint,Quantity,Value,LCSC Part #
"C101, C102",0603,2,22pF,C1653
C103,0603,1,100nF,C14663
"C104, C105",0603,2,1uF,C15849
U101,TQFP-32_7x7mm_P0.8mm,1,ATmega328PB-A,C132230
Y102,Crystal_SMD_HC49-SD,1,X49SM8MSD2SC,C12674
